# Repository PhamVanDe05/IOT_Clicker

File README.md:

# Classroom Clicker

Hệ thống trả lời trắc nghiệm trong lớp: sinh viên bấm đáp án trên tag cầm tay, giáo viên xem kết quả cả lớp ngay trên web.

## Cách hoạt động

1. Tag bấm **OK** thì phát gói `ANSWER` qua BLE, phát lại liên tục tới khi nhận ACK.
2. Gateway nghe gói, chuyển lên web qua USB Serial.
3. Web (Chrome/Edge, Web Serial) gọi `api.php`.
4. Server **lưu database xong mới trả ACK**; gói trùng không bị ghi 2 lần.
5. ACK đi ngược xuống trong khung `STATE`; tag thấy đúng MAC của mình thì dừng phát và hiện `b=`.

Định dạng từng byte: [`firmware/ClickerTag/protocol.h`](firmware/ClickerTag/protocol.h).

## Phần cứng

- **Tag:** nRF52840 SuperMini, bàn phím 3×4, 2 LED 7 đoạn qua 2×74HC595, motor rung, pin AAA.
- **Gateway:** nRF52840 SuperMini cắm USB laptop.

<table>
  <tr>
    <td align="center"><br>Vỏ tag</td>
    <td align="center"><br>Đáy tag</td>
    <td align="center"><br>Vỏ gateway</td>
  </tr>
  <tr>
    <td align="center"><br>Đáy gateway</td>
    <td align="center"><br>PCB tag, mặt trên</td>
    <td align="center"><br>PCB tag, mặt dưới</td>
  </tr>
  <tr>
    <td colspan="3" align="center"><br>Sơ đồ nguyên lý</td>
  </tr>
</table>

### Màn hình tag trong một buổi

Bảng mã đèn và mã lỗi đầy đủ: [docs/su_dung.md](docs/su_dung.md).

## Giao diện web

<table>
  <tr>
    <td align="center"><br>Trang chủ</td>
    <td align="center"><br>Đăng nhập</td>
  </tr>
  <tr>
    <td align="center"><br>Tổng quan</td>
    <td align="center"><br>Chuẩn bị lớp và bộ đề</td>
  </tr>
  <tr>
    <td align="center"><br>Tạo phòng, mã phòng</td>
    <td align="center"><br>Trực tiếp: câu hỏi và biểu đồ đáp án</td>
  </tr>
  <tr>
    <td align="center"><br>Phân tích câu hỏi</td>
    <td align="center"><br>Bảng kết quả</td>
  </tr>
</table>

## Thư mục

| Thư mục | Nội dung |
|---|---|
| `web/` | Web giáo viên và API |
| `schema.sql` | Cấu trúc database |
| `config.example.php` | Mẫu file cấu hình |
| `examples/` | Danh sách lớp và đề mẫu |
| `firmware/ClickerTag/` | Firmware tag sinh viên |
| `firmware/ClickerGateway/` | Firmware gateway cắm USB laptop |
| `hardware/` | PCB (KiCad, Gerber, BOM) và vỏ in 3D tag, gateway |
| `docs/su_dung.md` | Hướng dẫn sử dụng, bảng mã đèn và mã lỗi |

## Cài đặt nhanh

**Server**

1. Import `schema.sql` vào MariaDB.
2. Chép `config.example.php` ra ngoài thư mục web, điền database và khóa; trỏ biến môi trường `CLICKER_CONFIG` tới file đó.
3. Đặt `web/` dưới Apache, mở <http://localhost/clicker/> bằng Chrome hoặc Edge.

**Firmware**: Arduino IDE, core **Adafruit nRF52**, board **Adafruit ItsyBitsy nRF52840 Express**. Nạp `firmware/ClickerTag/` vào tag, `firmware/ClickerGateway/` vào gateway.

Hướng dẫn một buổi kiểm tra: [docs/su_dung.md](docs/su_dung.md).

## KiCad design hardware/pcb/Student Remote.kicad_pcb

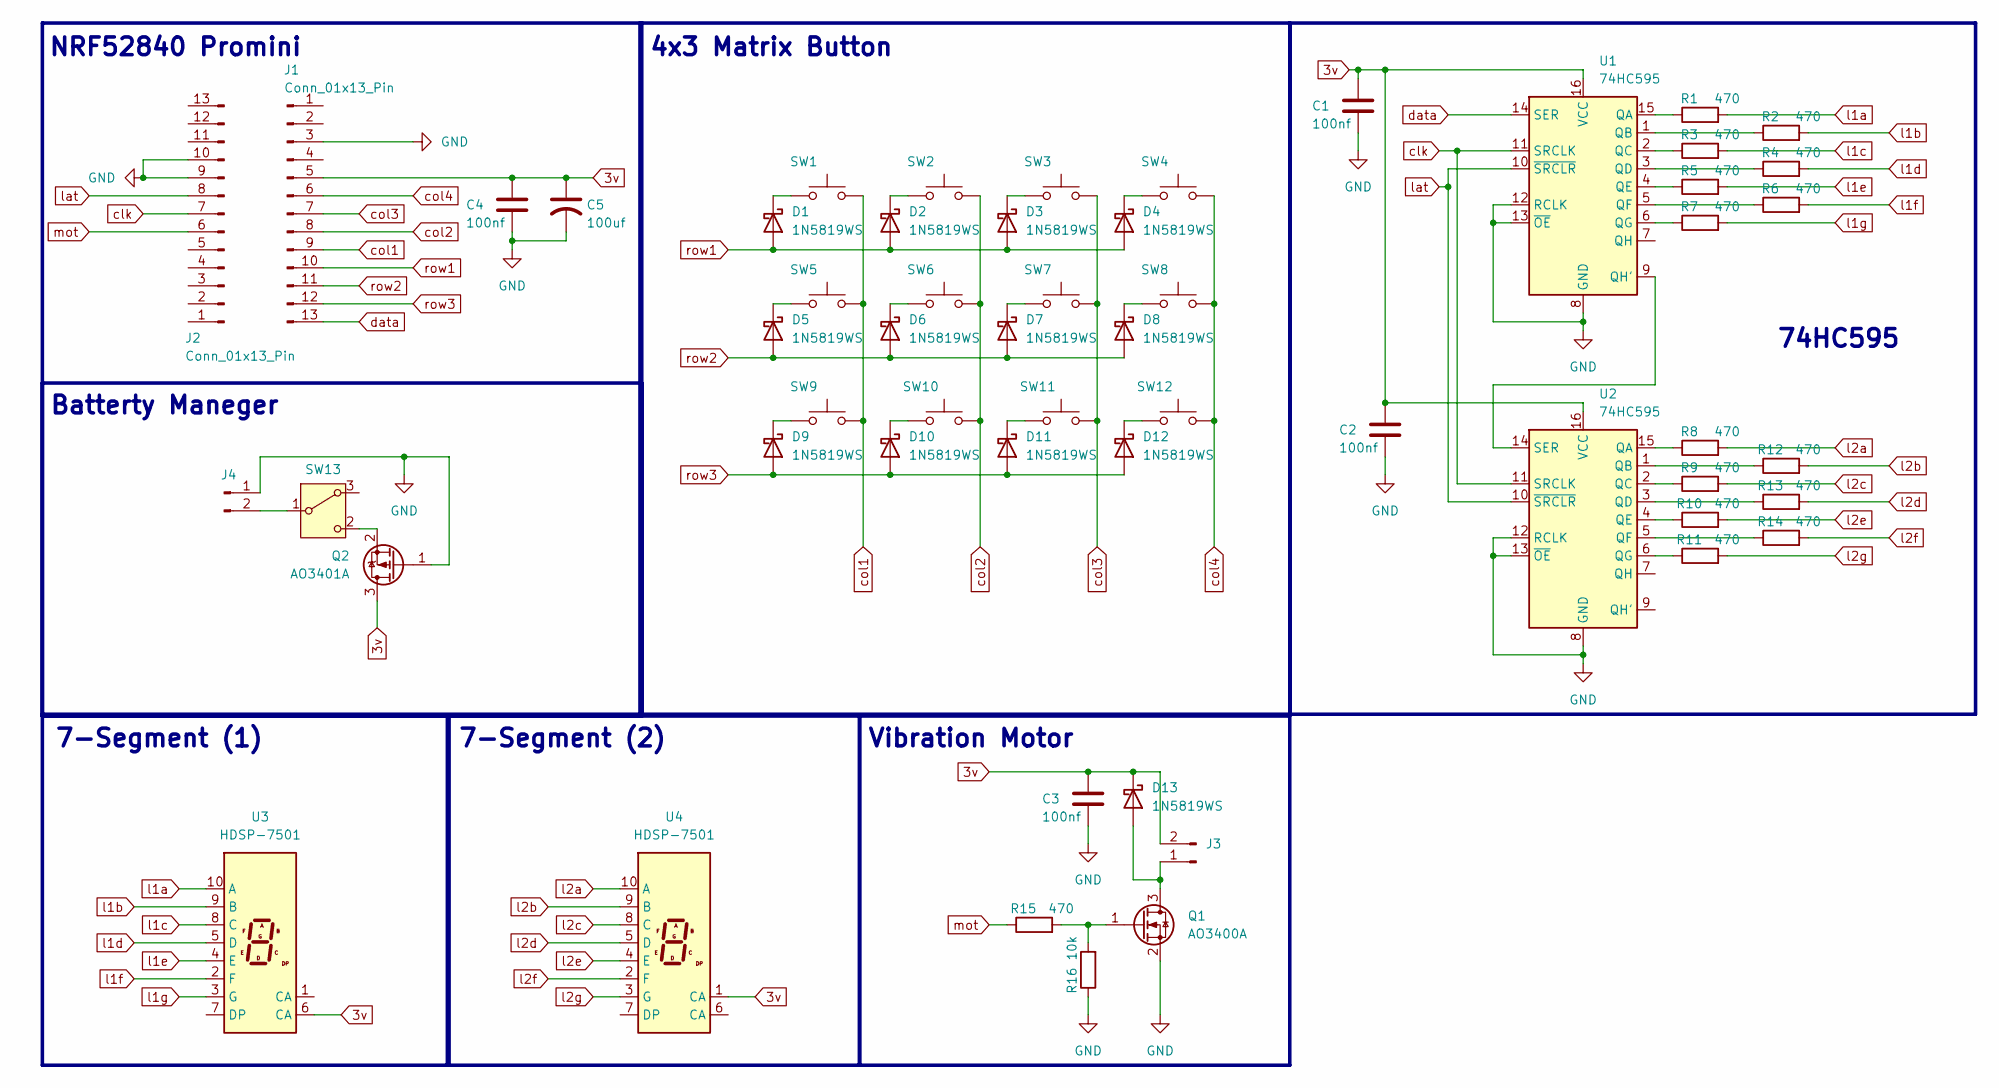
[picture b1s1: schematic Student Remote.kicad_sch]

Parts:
C1, C2, C3, C4: 100nf; C_0603_1608Metric_Pad1.08x0.95mm_HandSolder
C5: 100uf; CP_Elec_6.3x5.4
D1, D2, D3, D4, D5, D6, D7, D8, D9, D10, D11, D12, D13: 1N5819WS; D_SOD-323
J1, J2: Conn_01x13_Pin; PinHeader_1x13_P2.54mm_Vertical
J3, J4: Conn_01x02_Pin; PinHeader_1x02_P2.54mm_Vertical
Q1: AO3400A; SOT-23
Q2: AO3401A; SOT-23
R1, R2, R3, R4, R5, R6, R7, R8, R9, R10, R11, R12, R13, R14, R15: 470; R_0603_1608Metric_Pad0.98x0.95mm_HandSolder
R16: 10k; R_0603_1608Metric_Pad0.98x0.95mm_HandSolder
SW1, SW2, SW3, SW4, SW5, SW6, SW7, SW8, SW9, SW10, SW11, SW12: SW_Push; SW_SPST_SKQG_WithStem
SW13: SW_Wuerth_450301014042; SW_Slide-03_Wuerth-WS-SLTV_10x2.5x6.4_P2.54mm
U1, U2: 74HC595; SOIC-16_3.9x9.9mm_P1.27mm
U3, U4: HDSP-7501; HDSP-A151

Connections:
3v: C1.1, C2.1, C3.1, C4.1, C5.1, D13.1 (K), J1.5, J3.2, Q2.3 (D), U1.16 (VCC), U2.16 (VCC), U3.6 (CA), U4.1 (CA)
GND: C1.2, C2.2, C3.2, C4.2, C5.2, J1.3, J2.9, J2.10, J4.1, Q1.2 (S), Q2.1 (G), R16.1, U1.8 (GND), U1.12 (RCLK), U1.13 (~OE), U2.8 (GND), U2.12 (RCLK), U2.13 (~OE)
unnamed: D1.1 (K), SW1.1
unnamed: D2.1 (K), SW2.1
unnamed: D3.1 (K), SW3.1
unnamed: D4.1 (K), SW4.1
unnamed: D5.1 (K), SW5.1
unnamed: D6.1 (K), SW6.1
unnamed: D7.1 (K), SW7.1
unnamed: D8.1 (K), SW8.1
unnamed: D9.1 (K), SW9.1
unnamed: D10.1 (K), SW10.1
unnamed: D11.1 (K), SW11.1
unnamed: D12.1 (K), SW12.1
unnamed: D13.2 (A), J3.1, Q1.3 (D)
unnamed: J4.2, SW13.1 (B)
unnamed: Q1.1 (G), R15.2, R16.2
unnamed: Q2.2 (S), SW13.2 (C)
unnamed: R1.1, U1.15 (QA)
unnamed: R2.1, U1.1 (QB)
unnamed: R3.1, U1.2 (QC)
unnamed: R4.1, U1.3 (QD)
unnamed: R5.1, U1.4 (QE)
unnamed: R6.1, U1.5 (QF)
unnamed: R7.1, U1.6 (QG)
unnamed: U1.9 (QH'), U2.14 (SER)
unnamed: R8.1, U2.15 (QA)
unnamed: R12.1, U2.1 (QB)
unnamed: R9.1, U2.2 (QC)
unnamed: R13.1, U2.3 (QD)
unnamed: R10.1, U2.4 (QE)
unnamed: R14.1, U2.5 (QF)
unnamed: R11.1, U2.6 (QG)
clk: J2.7, U1.11 (SRCLK), U2.11 (SRCLK)
col1: J1.9, SW1.2, SW5.2, SW9.2
col2: J1.8, SW2.2, SW6.2, SW10.2
col3: J1.7, SW3.2, SW7.2, SW11.2
col4: J1.6, SW4.2, SW8.2, SW12.2
data: J1.13, U1.14 (SER)
l1a: R1.2, U3.10 (A)
l1b: R2.2, U3.9 (B)
l1c: R3.2, U3.8 (C)
l1d: R4.2, U3.5 (D)
l1e: R5.2, U3.4 (E)
l1f: R6.2, U3.2 (F)
l1g: R7.2, U3.3 (G)
l2a: R8.2, U4.10 (A)
l2b: R12.2, U4.9 (B)
l2c: R9.2, U4.8 (C)
l2d: R13.2, U4.5 (D)
l2e: R10.2, U4.4 (E)
l2f: R14.2, U4.2 (F)
l2g: R11.2, U4.3 (G)
lat: J2.8, U1.10 (~SRCLR), U2.10 (~SRCLR)
mot: J2.6, R15.1
row1: D1.2 (A), D2.2 (A), D3.2 (A), D4.2 (A), J1.10
row2: D5.2 (A), D6.2 (A), D7.2 (A), D8.2 (A), J1.11
row3: D9.2 (A), D10.2 (A), D11.2 (A), D12.2 (A), J1.12

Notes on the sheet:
Batterty Maneger
74HC595
4x3 Matrix Button
NRF52840 Promini
7-Segment (2)
7-Segment (1)
Vibration Motor

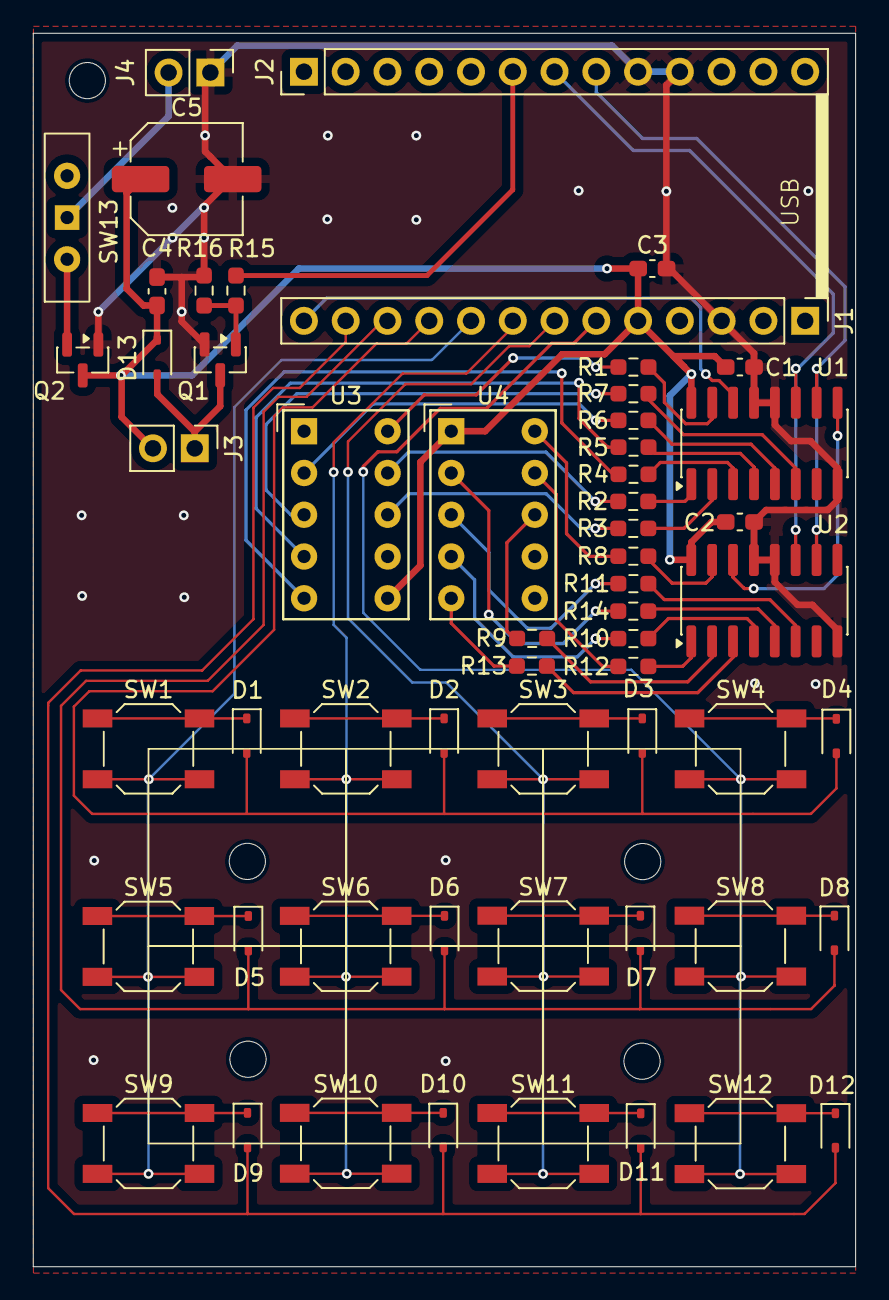
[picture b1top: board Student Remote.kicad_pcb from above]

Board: 2 copper layers, 50.0 x 75.0 mm, 57 parts (0 on the bottom side), 58 nets.

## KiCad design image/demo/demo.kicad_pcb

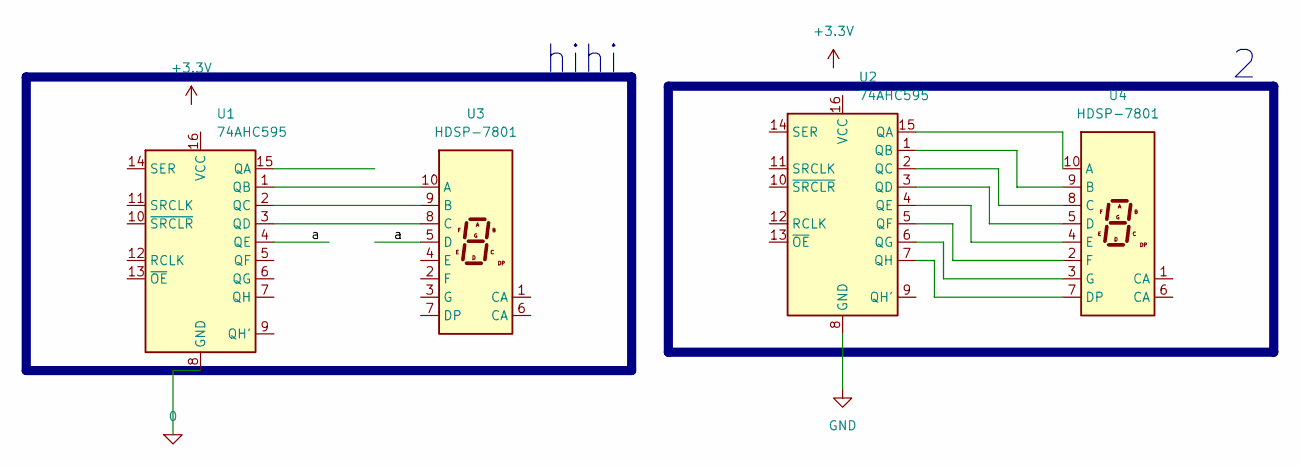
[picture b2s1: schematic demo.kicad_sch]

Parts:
U1, U2: 74AHC595; CERDIP-16_W7.62mm_SideBrazed_LongPads
U3, U4: HDSP-7801

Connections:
0: U1.8 (GND)
/a: U1.4 (QE), U3.5 (D)
GND: U2.8 (GND)
unnamed: U1.1 (QB), U3.10 (A)
unnamed: U1.2 (QC), U3.9 (B)
unnamed: U1.3 (QD), U3.8 (C)
unnamed: U2.15 (QA), U4.10 (A)
unnamed: U2.1 (QB), U4.9 (B)
unnamed: U2.2 (QC), U4.8 (C)
unnamed: U2.3 (QD), U4.5 (D)
unnamed: U2.4 (QE), U4.4 (E)
unnamed: U2.5 (QF), U4.2 (F)
unnamed: U2.6 (QG), U4.3 (G)
unnamed: U2.7 (QH), U4.7 (DP)

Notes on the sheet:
hihi

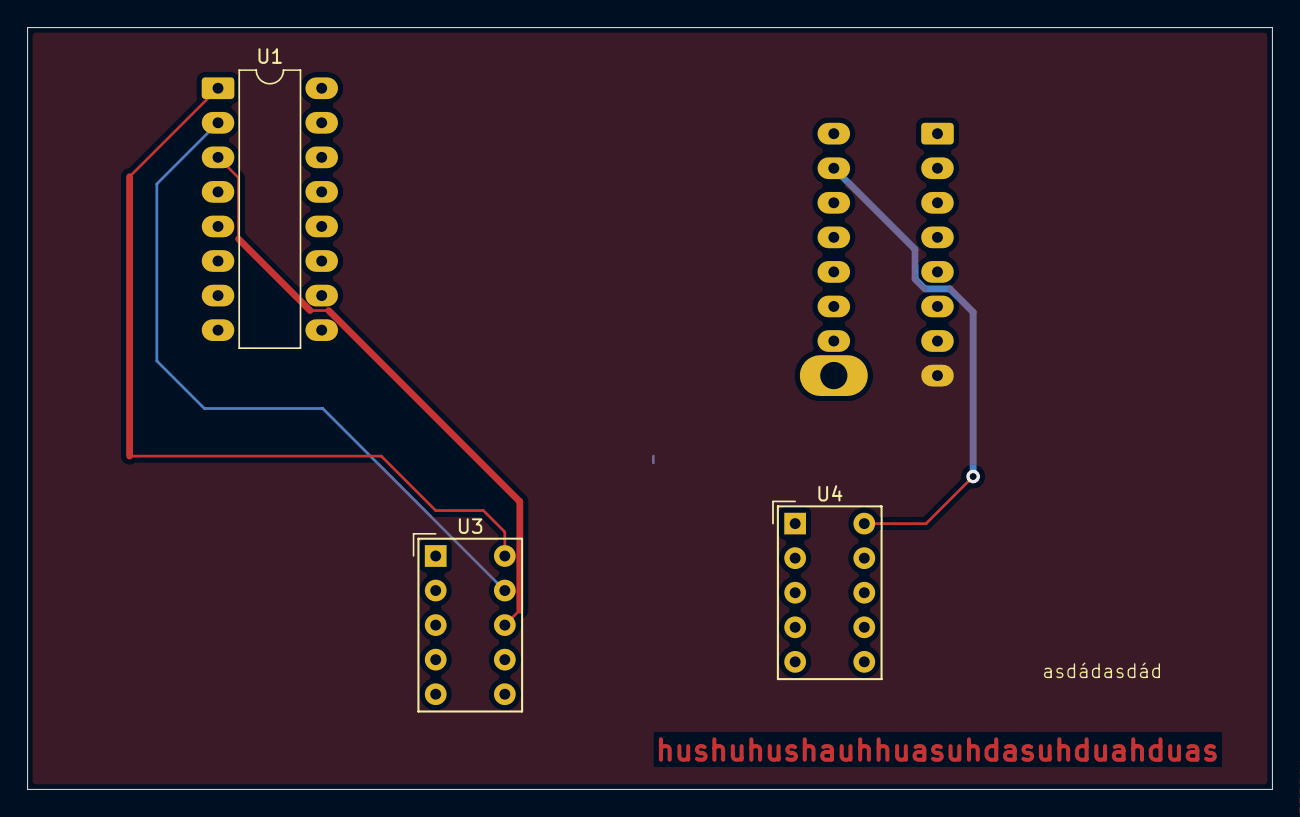
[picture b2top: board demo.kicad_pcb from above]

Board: 2 copper layers, 91.5 x 56.0 mm, 4 parts (1 on the bottom side), 12 nets.

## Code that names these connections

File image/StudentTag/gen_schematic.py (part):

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          fields=((-1.27, -18.8, 'left'), (-1.27, -16.51, 'left')), footprint='Connector_PinSocket_2.54mm:PinSocket_1x13_P2.54mm_Vertical')
wire(J2[10], (24.13, J2[10][1]), (24.13, J2[9][1]), J2[9])
power('GND', (24.13, J2[9][1]), rot=270, fields=((-5.08, 0, 'right'), (-5.08, 0, 'right')))
for pin, name, x in [(8, 'lat', 16.51), (7, 'clk', 24.13), (6, 'mot', 16.51)]:
    wire(J2[pin], (x, J2[pin][1])); label(name, (x, J2[pin][1]), 'left', shape='input')
wire(J1[3], (62.23, J1[3][1])); power('GND', (62.23, J1[3][1]), rot=90, fields=((5.08, 0, 'left'), (5.08, 0, 'left')))
for pin, name in zip(range(6, 14), ['col4', 'col3', 'col2', 'col1', 'row1', 'row2', 'row3', 'data']):
    x = 62.23 if pin % 2 == 0 else 54.61                  # staggered like the reference
    wire(J1[pin], (x, J1[pin][1])); label(name, (x, J1[pin][1]), 'right', shape='input')
rail = J1[5][1]
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    if i == 0:
        wire(U[14], (207.01, U[14][1])); label('data', (207.01, U[14][1]), 'left', shape='input')
        wire((207.01, U[11][1]), (CLK, U[11][1])); label('clk', (207.01, U[11][1]), 'left', shape='input')
        wire((204.47, U[12][1]), (LAT, U[12][1])); label('lat', (204.47, U[12][1]), 'left', shape='input')
        first = U
    else:
        wire((CLK, first[11][1]), (CLK, U[11][1])); wire((LAT, first[12][1]), (LAT, U[12][1]))
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power('GND', (C3[2][0], C3[2][1] + 2.54)); wire(C3[2], (C3[2][0], C3[2][1] + 2.54))
wire(D13[2], (163.83, 130.81), (168.91, 130.81))
wire(J3[1], (168.91, 130.81), Q1[3])
label('mot', (143.51, 139.7), 'left', shape='input')
wire((143.51, 139.7), R15[1]); wire(R15[2], (157.48, 139.7), Q1[1]); wire((157.48, 139.7), R16[1])
for p in (R16[2], Q1[2]):
    wire(p, (p[0], 151.13)); power('GND', (p[0], 151.13))
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         ['uuid', Q(ROOT)], ['paper', Q('A4')],
         ['title_block', ['title', Q('Student Tag — nRF52840 BLE clicker')], ['date', Q('2026-09-28')], ['rev', Q('B')],
          ['company', Q('Classroom Clicker')],
          ['comment', '1', Q('Vẽ như image/mau.png, đã sửa: 74HC595 RCLK ← lat, SRCLR → 3v; Q2 D phía pin')],
          ['comment', '2', Q('Sinh bằng image/StudentTag/gen_schematic.py — sửa script rồi chạy lại, không sửa tay')]],
         ['lib_symbols', *lib_symbols.values()], *items,
         ['sheet_instances', ['path', Q('/'), ['page', Q('1')]]], ['embedded_fonts', 'no']]
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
